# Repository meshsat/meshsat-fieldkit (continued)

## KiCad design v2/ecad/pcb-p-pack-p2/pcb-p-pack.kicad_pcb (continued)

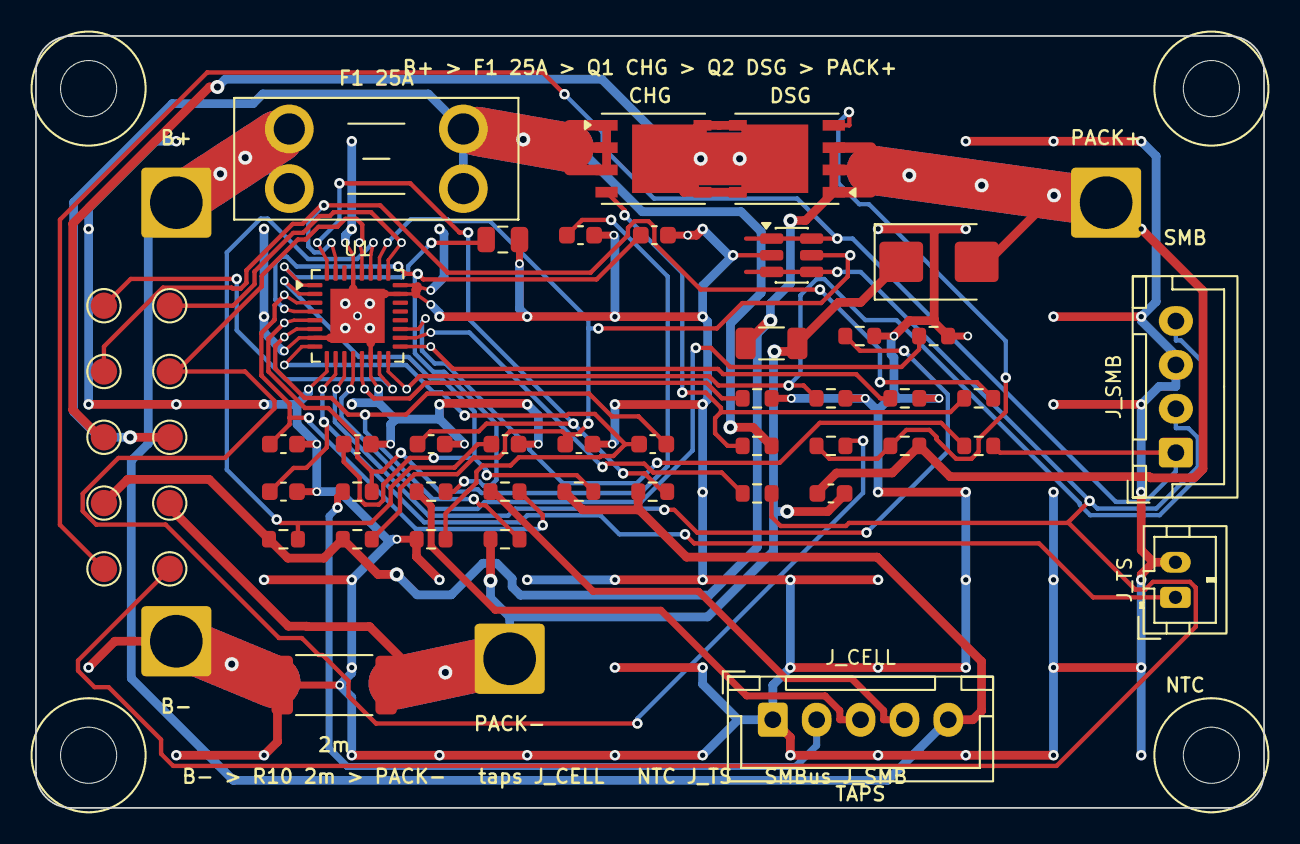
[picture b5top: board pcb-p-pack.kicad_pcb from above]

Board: 2 copper layers, 70.0 x 44.0 mm, 60 parts (0 on the bottom side), 35 nets.

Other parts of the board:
H1, H2, H3, H4: M3 into the enclosure boss; MountingHole_3.2mm_M3

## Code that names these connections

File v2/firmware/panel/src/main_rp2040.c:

/*
 * main_rp2040.c: the panel controller's main loop on the RP2040 (pico-sdk). NOT BUILT HERE (no arm toolchain on this
 * host); prototype firmware for an unbuilt board.
 *
 * Order (FW-C01, FW-C02): PI_KILL low and PI_SHDN_REQ released first; ZEROIZE_SW and the SLOT_EN pads read as inputs;
 * the core decides each SLOT_EN's first level (all low with the toggle closed or a wipe pending); the watchdog; then
 * the 1 ms loop, in which the core runs the rest of the boot order (the wipe table, the expanders, the charger (owed),
 * HOT-R1, the slots one at a time).
 *
 * Not here, and owed (README.md section 4): the USB device and the bridge protocol (MESHSAT-837, wire format not
 * defined), the e-paper's command layer, the charger's registers (FW-A rows), the secure element's command layer
 * (CryptoAuthLib, not vendored), the VEML7700 and TMP117 reads.
 */
#include <stdbool.h>

#include "hal.h"
#include "panel.h"

void hal_init_rest(void);

static panel_t P;

/* FW-K04: after a failed transfer, a held SDA is released by nine SCL pulses and a STOP, and the event is logged */
static void bb_scl(void *c, bool l) { (void)c; hal_i2c_bitbang_scl(l); }
static bool bb_sda(void *c) { (void)c; return hal_i2c_bitbang_sda_read(); }
static void bb_stop(void *c) { (void)c; hal_i2c_bitbang_stop(); }
static void bb_delay(void *c, unsigned us) { (void)c; hal_delay_us(us); }
static const panel_bitbang_t BB = { 0, bb_scl, bb_sda, bb_stop, bb_delay };

static int recover_if_held(int r)
{
    if (r == 0)
        return 0;
    hal_i2c_bitbang_begin();
    if (!hal_i2c_bitbang_sda_read()) {
        int pulses = panel_bus_recover(&BB);
        panel_ev_report(&P, EV_I2C_RECOVERED, (uint8_t)(pulses < 0 ? 0xFF : pulses), hal_now_ms());
    }
    hal_i2c_bitbang_end();
    return r;
}

static int bus_write(void *ctx, uint8_t addr, const uint8_t *buf, unsigned len)
{
    (void)ctx;
    return recover_if_held(hal_i2c_write(addr, buf, len, hal_now_ms() + HAL_I2C_OP_TIMEOUT_MS));
}

static int bus_read(void *ctx, uint8_t addr, uint8_t reg, uint8_t *buf, unsigned len)
{
    (void)ctx;
    ms_t d = hal_now_ms() + HAL_I2C_OP_TIMEOUT_MS;
    if (hal_i2c_write(addr, &reg, 1, d) != 0)
        return recover_if_held(-1);
    return recover_if_held(hal_i2c_read(addr, buf, len, d));
}

static ms_t z_now(void *ctx) { (void)ctx; return hal_now_ms(); }

/* The secure element's two GenKey modes go through CryptoAuthLib (atcab_genkey, atcab_get_pubkey) with the panel's
 * six-function HAL bounded as ZEROIZE.md 3.4 (a) and (b) set out. The library is not vendored in this tree: OWED. Until
 * it is, every SE call fails, so the boot table takes "the SE does not answer" (normal boot without the SE, MASTER WARN)
 * and a ZEROIZE commit ends INCOMPLETE with the slots held off: fail secure. */
static int se_create(void *ctx, uint8_t slot, uint8_t pub[64], ms_t deadline)
{
    (void)ctx; (void)slot; (void)pub; (void)deadline;
    return -1;
}
static int se_public(void *ctx, uint8_t slot, uint8_t pub[64], ms_t deadline)
{
    (void)ctx; (void)slot; (void)pub; (void)deadline;
    return -1;
}
static bool se_recorded(void *ctx, uint8_t slot, uint8_t pub[64])
{
    (void)ctx; (void)slot; (void)pub;
    return false;                            /* P_A0 and P_B0 are written at enrolment (ZEROIZE.md 3.3): owed */
}
static void arm_cut(void *ctx, ms_t at) { (void)ctx; hal_arm_slot_cut_alarm(at); }
static void tell_modules(void *ctx) { (void)ctx; /* over the bridge protocol: owed (F-02) */ }
static void feed(void *ctx) { (void)ctx; hal_watchdog_feed(); }
static int fl_read(void *ctx, uint32_t off, uint8_t *buf, unsigned len) { (void)ctx; return hal_journal_read(off, buf, len); }
static int fl_prog(void *ctx, uint32_t off, const uint8_t *buf, unsigned len) { (void)ctx; return hal_journal_program(off, buf, len); }
static int fl_erase(void *ctx) { (void)ctx; return hal_journal_erase(); }
static void epd_send(void *ctx, uint8_t page, bool full) { (void)ctx; (void)page; (void)full; /* owed */ }
static int ss_read(void *ctx, uint32_t off, uint8_t *buf, unsigned len) { (void)ctx; return hal_slotstore_read(off, buf, len); }
static int ss_prog(void *ctx, uint32_t off, const uint8_t *buf, unsigned len) { (void)ctx; return hal_slotstore_program(off, buf, len); }
static int ss_erase(void *ctx) { (void)ctx; return hal_slotstore_erase(); }

static const panel_ops_t OPS = {
    .bus = { 0, bus_write, bus_read },
    .zer = { 0, z_now, se_create, se_public, se_recorded, arm_cut, tell_modules, feed, fl_read, fl_prog, fl_erase,
             8192u },
    .epd = { 0, epd_send },
    .slots = { 0, ss_read, ss_prog, ss_erase, 4096u },
};

int main(void)
{
    hal_init_pins_first();                                   /* FW-C01 steps 1 and 2 */
    bool zer_closed = !hal_gpio_get(HAL_GPIO_ZEROIZE_SW);    /* step 3: the level, at the first instruction */
    bool held[3], drive[3];
    hal_slot_en_read(held);                                  /* FW-C02 */
    panel_init(&P, &OPS, hal_now_ms(), zer_closed, held, hal_reset_was_power_on(), drive);   /* FW-C05 (F-15) */
    hal_slot_en_drive_initial(drive);
    panel_ev_report(&P, EV_BOOT, (uint8_t)hal_reset_reason(), hal_now_ms());   /* FW-C02: the boot reason logged */
    hal_init_rest();
    hal_watchdog_start(PANEL_WATCHDOG_MS);

    panel_in_t in = { 0 };
    panel_out_t out;
    in.br.display_slot = -1;
    in.br.soc_pct = -1;
    ms_t last = hal_now_ms();
    for (;;) {
        ms_t now = hal_now_ms();
        if (now == last) {
            continue;
        }
        last = now;
        in.test_sw = hal_gpio_get(HAL_GPIO_TEST_SW);
        in.sos_sw = hal_gpio_get(HAL_GPIO_SOS_SW);
        in.zeroize_sw = hal_gpio_get(HAL_GPIO_ZEROIZE_SW);
        in.emcon_rd = hal_gpio_get(HAL_GPIO_EMCON_RD_R);
        in.tr_aprs = hal_gpio_get(HAL_GPIO_TR_APRS);
        in.exp_int = hal_gpio_get(HAL_GPIO_EXP_INT);
        in.hb[0] = hal_gpio_get(HAL_GPIO_HB1);
        in.hb[1] = hal_gpio_get(HAL_GPIO_HB2);
        in.hb[2] = hal_gpio_get(HAL_GPIO_HB3);
        in.pi_shdn_req = hal_gpio_get(HAL_GPIO_PI_SHDN_REQ);
        in.pi_button = false;                                /* HAL_PI_BUTTON_WIRED 0: finding F-01 */
        in.epd_busy = hal_gpio_get(HAL_GPIO_EPD_BUSY);
        in.rail_mv = hal_rail_sense_mv();

        panel_tick(&P, now, &in, &out);

        hal_gpio_put(HAL_GPIO_PI_KILL, out.pi_kill);
        hal_pi_shdn_req_assert(out.pi_shdn_assert);
        hal_gpio_put(HAL_GPIO_SLOT_EN1, out.slot_en[0]);
        hal_gpio_put(HAL_GPIO_SLOT_EN2, out.slot_en[1]);
        hal_gpio_put(HAL_GPIO_SLOT_EN3, out.slot_en[2]);
        hal_gpio_put(HAL_GPIO_HDMI_SEL1, out.hdmi_sel1);
        hal_gpio_put(HAL_GPIO_HDMI_SEL2, out.hdmi_sel2);
        hal_gpio_put(HAL_GPIO_SHORE_INHIBIT, out.shore_inhibit);
        hal_gpio_put(HAL_GPIO_EPD_PWR_n, !out.epd_power);
        hal_gpio_put(HAL_GPIO_LED_STAT, out.led_stat);
        hal_pwm_set_permille(HAL_GPIO_PANEL_PWM, out.pwm_permille);
        hal_pwm_set_permille(HAL_GPIO_PWM1, out.sounder ? 1000u : 0u);
        hal_watchdog_feed();
    }
}

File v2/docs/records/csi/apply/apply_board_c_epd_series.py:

#!/usr/bin/env python3
"""Board C's four e-paper lines take a series termination at the RP2040's pins (stream csi, MESHSAT-1357, 29 September
2026; session decision CSI-D3). A DRAFT for the owner of gen_sch_c.py, applied by the integrator; nothing is regenerated.

WHAT IT CHANGES
  tools/gen_sch_c.py  U3's pins 4 to 7 (GPIO2 to GPIO5) move to EPD_SCL_R, EPD_SDA_R, EPD_DC_R and EPD_CS_R, and four
                      27R resistors join each to its line: R53 EPD_SCL, R54 EPD_SDA, R55 EPD_DC, R56 EPD_CS. The lines keep
                      their names from the resistor to J_EPD, so every far-end record and every reader of J_EPD is unchanged.
  tools/boards/c.json four signal-class entries, EPD_SCL_R, EPD_SDA_R, EPD_DC_R and EPD_CS_R (CLOCKED_DIGITAL), ahead of
                      the glob EPD_*, which is LOW_SPEED_OR_DC and would otherwise take the new nets.
WHY 27R: the value the maker series-terminates this chip's own USB pins with (hardware design guide p. 12, "these I/Os do
require 27 Ω series termination resistors"), inside SI-001's 10 to 150 ohm screen, and a part this tree already codes
(lcsc_fill.py: 27R on R_0603, C25190). Raspberry Pi publishes no GPIO output impedance, so the value cannot be computed to
a match: it is INFERRED, and the edge at J_EPD is the bring-up measurement owed.

HOW IT BEHAVES: every anchor is asserted to occur exactly once; the preconditions are checked first and a failed one
refuses in one sentence with exit code 2 (a second run is one); the new generator is parsed (ast) and its U3 map and the
four resistor calls are read back from the parse; c.json is written in its own format (indent 1) and read back.
--dry-run writes nothing. --root <tree> runs on another tree (a scratch view).
After it: regenerate board C's schematic, netlist and intent on the box, then readback_board_c_epd_series.py on the new
netlist, then SI-001 re-taken (see the stream's README)."""
import ast, json, os, re, sys

ROOT = os.path.abspath(os.path.join(os.path.dirname(os.path.abspath(__file__)), "..", "..", "..", "..", ".."))
LINES = (("4", "EPD_SCL", "R53"), ("5", "EPD_SDA", "R54"), ("6", "EPD_DC", "R55"), ("7", "EPD_CS", "R56"))
OLD_U3 = '4: "EPD_SCL", 5: "EPD_SDA", 6: "EPD_DC", 7: "EPD_CS"'
NEW_U3 = '4: "EPD_SCL_R", 5: "EPD_SDA_R", 6: "EPD_DC_R", 7: "EPD_CS_R"'
ANCHOR = 'r("R2", "27R", "USB_DP_R", "USB_PNL_P"); r("R3", "27R", "USB_DM_R", "USB_PNL_N");'
ADD = ('# THE E-PAPER LINES ARE SERIES-TERMINATED AT THE CONTROLLER (stream csi, CSI-D3, 29 September 2026, taken under the\n'
       '# owner\'s standing rule of 26 September 2026). SI-001 found EPD_SCL, EPD_SDA, EPD_DC and EPD_CS layout-bound: the RP2040 publishes no\n'
       '# edge (no IBIS model, no minimum transition) and the lines run from the cluster to J_EPD. 27R at each pin, the value the maker\n'
       '# series-terminates this chip\'s USB pins with (hardware design guide p. 12); INFERRED for a GPIO pad, the edge at J_EPD is owed\n'
       '# at bring-up. Place each within a few millimetres of U3\'s pin (the layout generator\'s item). Reverse: delete the four lines\n'
       '# below and put U3 pins 4 to 7 back on EPD_SCL, EPD_SDA, EPD_DC and EPD_CS.\n'
       'r("R53", "27R", "EPD_SCL_R", "EPD_SCL"); r("R54", "27R", "EPD_SDA_R", "EPD_SDA"); r("R55", "27R", "EPD_DC_R", "EPD_DC"); r("R56", "27R", "EPD_CS_R", "EPD_CS")\n')
BASIS = {"EPD_SCL": "the e-paper's SPI clock", "EPD_SDA": "the e-paper's SPI data (the panel answers on it in a read)",
         "EPD_DC": "the e-paper's data and command select", "EPD_CS": "the e-paper's chip select"}


def refuse(why):
    print("apply_board_c_epd_series: refused: %s" % why); sys.exit(2)


def netlist_refs(path):
    """Every component reference of a KiCad netlist, parsed from its components section."""
    txt = open(path, encoding="utf-8", errors="replace").read()
    return set(re.findall(r'\(comp \(ref "([^"]+)"\)', txt))


def u3_map(tree):
    """U3's pin map as the generator writes it: the dict literal of the synth("U3", ...) call, read from the parse."""
    for node in ast.walk(tree):
        if isinstance(node, ast.Call) and getattr(node.func, "id", None) == "synth" and node.args and \
           isinstance(node.args[0], ast.Constant) and node.args[0].value == "U3":
            return ast.literal_eval(node.args[4])
    return None


def r_calls(tree):
    """{ref: (value, net a, net b)} of every r(...) call whose arguments are literals."""
    out = {}
    for node in ast.walk(tree):
        if isinstance(node, ast.Call) and getattr(node.func, "id", None) == "r" and len(node.args) >= 4 and \
           all(isinstance(a, ast.Constant) for a in node.args[:4]):
            out[node.args[0].value] = tuple(a.value for a in node.args[1:4])
    return out


def main(argv):
    root = os.path.abspath(argv[argv.index("--root") + 1]) if "--root" in argv else ROOT
    dry = "--dry-run" in argv
    gen = os.path.join(root, "v2", "ecad", "tools", "gen_sch_c.py")
    tab = os.path.join(root, "v2", "ecad", "tools", "boards", "c.json")
    net = os.path.join(root, "v2", "ecad", "pcb-c-display-c8", "out", "pcb-c-display.net")
    for p in (gen, tab, net):
        if not os.path.isfile(p): refuse("%s is not in the tree at %s" % (os.path.relpath(p, root), root))
    src = open(gen, encoding="utf-8").read()
    tree = ast.parse(src)
    m = u3_map(tree)
    if m is None: refuse("gen_sch_c.py has no synth(\"U3\", ...) call to read U3's pins from")
    if m.get(7) == "EPD_CS_R" or any(r in r_calls(tree) for _p, _n, r in LINES):
        refuse("gen_sch_c.py already carries the series resistors (a second run)")
    for p, n, _r in LINES:
        if m.get(int(p)) != n: refuse("U3 pin %s is on %r, not %s" % (p, m.get(int(p)), n))
    for a in (OLD_U3, ANCHOR):
        if src.count(a) != 1: refuse("the anchor %r occurs %d times in gen_sch_c.py, not once" % (a[:50], src.count(a)))
    used = netlist_refs(net) | set(r_calls(tree))
    taken = [r for _p, _n, r in LINES if r in used]
    if taken: refuse("the references %s are taken on board C" % ", ".join(taken))
    raw = open(tab, encoding="utf-8").read()
    d = json.loads(raw)
    if json.dumps(d, indent=1, ensure_ascii=False) + "\n" != raw: refuse("boards/c.json is not in the format this writes")
    pats = [e.get("pattern") for e in d.get("signal_classes") or []]
    if any(n + "_R" in pats for _p, n, _r in LINES): refuse("boards/c.json already declares the new nets")
    for n in ("EPD_DC", "EPD_*"):
        if pats.count(n) != 1: refuse("boards/c.json declares %r %d times, not once" % (n, pats.count(n)))
    if not pats.index("EPD_DC") < pats.index("EPD_*"): refuse("EPD_DC is not declared ahead of EPD_*")

    new = src.replace(OLD_U3, NEW_U3).replace(ANCHOR, ANCHOR, 1)
    i = new.index(ANCHOR); j = new.index("\n", i) + 1
    new = new[:j] + ADD + new[j:]
    assert new != src
    t2 = ast.parse(new)
    m2, rc = u3_map(t2), r_calls(t2)
    for p, n, r in LINES:
        assert m2.get(int(p)) == n + "_R", (p, m2.get(int(p)))
        assert rc.get(r) == ("27R", n + "_R", n), (r, rc.get(r))
    ins = pats.index("EPD_DC") + 1
    for k, (_p, n, _r) in enumerate(LINES):
        d["signal_classes"].insert(ins + k, {"pattern": n + "_R", "class": "CLOCKED_DIGITAL", "basis": (
            "%s between the RP2040's pin and its 27R series termination, a few millimetres; the same edges as %s "
            "(29 September 2026, stream csi, CSI-D3)" % (BASIS[n], n))})
    out = json.dumps(d, indent=1, ensure_ascii=False) + "\n"
    assert out != raw
    if dry:
        print("apply_board_c_epd_series: dry run, nothing written: U3 pins 4 to 7 to the _R nets, R53 to R56 27R, four "
              "class entries ahead of EPD_*")
        return 0
    open(gen, "w", encoding="utf-8").write(new)
    open(tab, "w", encoding="utf-8").write(out)
    t3 = ast.parse(open(gen, encoding="utf-8").read())
    assert u3_map(t3).get(7) == "EPD_CS_R" and all(r in r_calls(t3) for _p, _n, r in LINES)
    back = [e["pattern"] for e in json.load(open(tab, encoding="utf-8"))["signal_classes"]]
    assert all(back.index(n + "_R") < back.index("EPD_*") for _p, n, _r in LINES)
    print("apply_board_c_epd_series: written: gen_sch_c.py (U3 pins 4 to 7, R53 to R56 27R) and boards/c.json (four "
          "class entries). Owed: board C regenerated on the box, readback_board_c_epd_series.py on the new netlist, the "
          "four resistors placed at U3's pins by gen_pcb_c3.py, SI-001 re-taken")
    return 0


if __name__ == "__main__":
    sys.exit(main(sys.argv[1:]))

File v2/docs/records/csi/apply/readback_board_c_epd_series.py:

#!/usr/bin/env python3
"""The netlist read-back of apply_board_c_epd_series.py (stream csi, CSI-D3, 29 September 2026): run it on board C's
regenerated netlist. It parses the netlist (every net to its last, as edge_length.read_netlist reads it) and holds each
e-paper line to what the draft asks, printing one line per check:
  * U3's pin (4 GPIO2, 5 GPIO3, 6 GPIO4, 7 GPIO5) sits on <line>_R, and <line>_R carries nothing but that pin and pin 1 of
    its resistor (the stub between the controller and its termination);
  * the resistor (R53 to R56) is 27R and its pin 2 is on <line>;
  * <line> carries J_EPD's pin (12 CSB, 11 DC, 13 SCL, 14 SDA) and no U3 pin.
Exit 0 when every check holds, 1 when one does not (the committed netlist before the draft is the failing case), 2 on
usage. Usage: readback_board_c_epd_series.py <board C netlist>"""
import os, re, sys

CHECKS = (("EPD_SCL", "4", "R53", "13"), ("EPD_SDA", "5", "R54", "14"), ("EPD_DC", "6", "R55", "11"), ("EPD_CS", "7", "R56", "12"))


def read(path):
    txt = open(path, encoding="utf-8", errors="replace").read()
    nets = {}
    for m in re.finditer(r'\(net \(code "?\d+"?\) \(name "([^"]*)"\)(?: \(class "([^"]*)"\))?(.*?)(?=\(net \(code|\Z)', txt, re.S):
        nets[m.group(1).lstrip("/")] = set(re.findall(r'\(node \(ref "([^"]+)"\) \(pin "([^"]+)"\)', m.group(3)))
    values = dict(re.findall(r'\(comp \(ref "([^"]+)"\)\s*\(value "([^"]*)"\)', txt))
    return nets, values


def main(argv):
    if not argv: print(__doc__); return 2
    nets, values = read(argv[0])
    bad = 0
    def say(ok, words):
        nonlocal bad
        bad += 0 if ok else 1
        print("  %s %s" % ("HOLDS" if ok else "FAILS", words))
    for line, pin, ref, jpin in CHECKS:
        stub = nets.get(line + "_R")
        say(stub == {("U3", pin), (ref, "1")}, "%s_R carries U3 pin %s and %s pin 1 only (reads %s)" % (
            line, pin, ref, sorted(stub) if stub is not None else "no such net"))
        say(values.get(ref) == "27R", "%s is 27R (reads %r)" % (ref, values.get(ref)))
        far = nets.get(line, set())
        say((ref, "2") in far and ("J_EPD", jpin) in far, "%s carries %s pin 2 and J_EPD pin %s" % (line, ref, jpin))
        say(not any(r == "U3" for r, _p in far), "%s carries no U3 pin" % line)
    print("readback_board_c_epd_series: %s (%d check(s) failing)" % ("HOLDS" if not bad else "FAILS", bad))
    return 0 if not bad else 1


if __name__ == "__main__":
    sys.exit(main(sys.argv[1:]))
